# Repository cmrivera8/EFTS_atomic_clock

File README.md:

# EFTS_atomic_clock
The atomic clock described in this repository is used in the yearly European Frequency and Time Seminar (EFTS) hosted at ENSMM. This repository contains the original design files as well as the improved control software GUI in python (EFTS_atomic_clock/mac_control_program/qt_mac.py) and the microcontroller code (EFTS_atomic_clock/mac/mac.ino) embedded in the demonstrator.

When I started my contribution on this project, there were three atomic clocks, out of which only one was working correctly. The other two were marginally operational, with a weak absorption signal and low signal-to-noise ratio. This made it very difficult to lock the servo loops on the desired electronic transition. Moreover, the GUI was not intuitive and resulted in a not-ideal learning experience for the seminar attendees.

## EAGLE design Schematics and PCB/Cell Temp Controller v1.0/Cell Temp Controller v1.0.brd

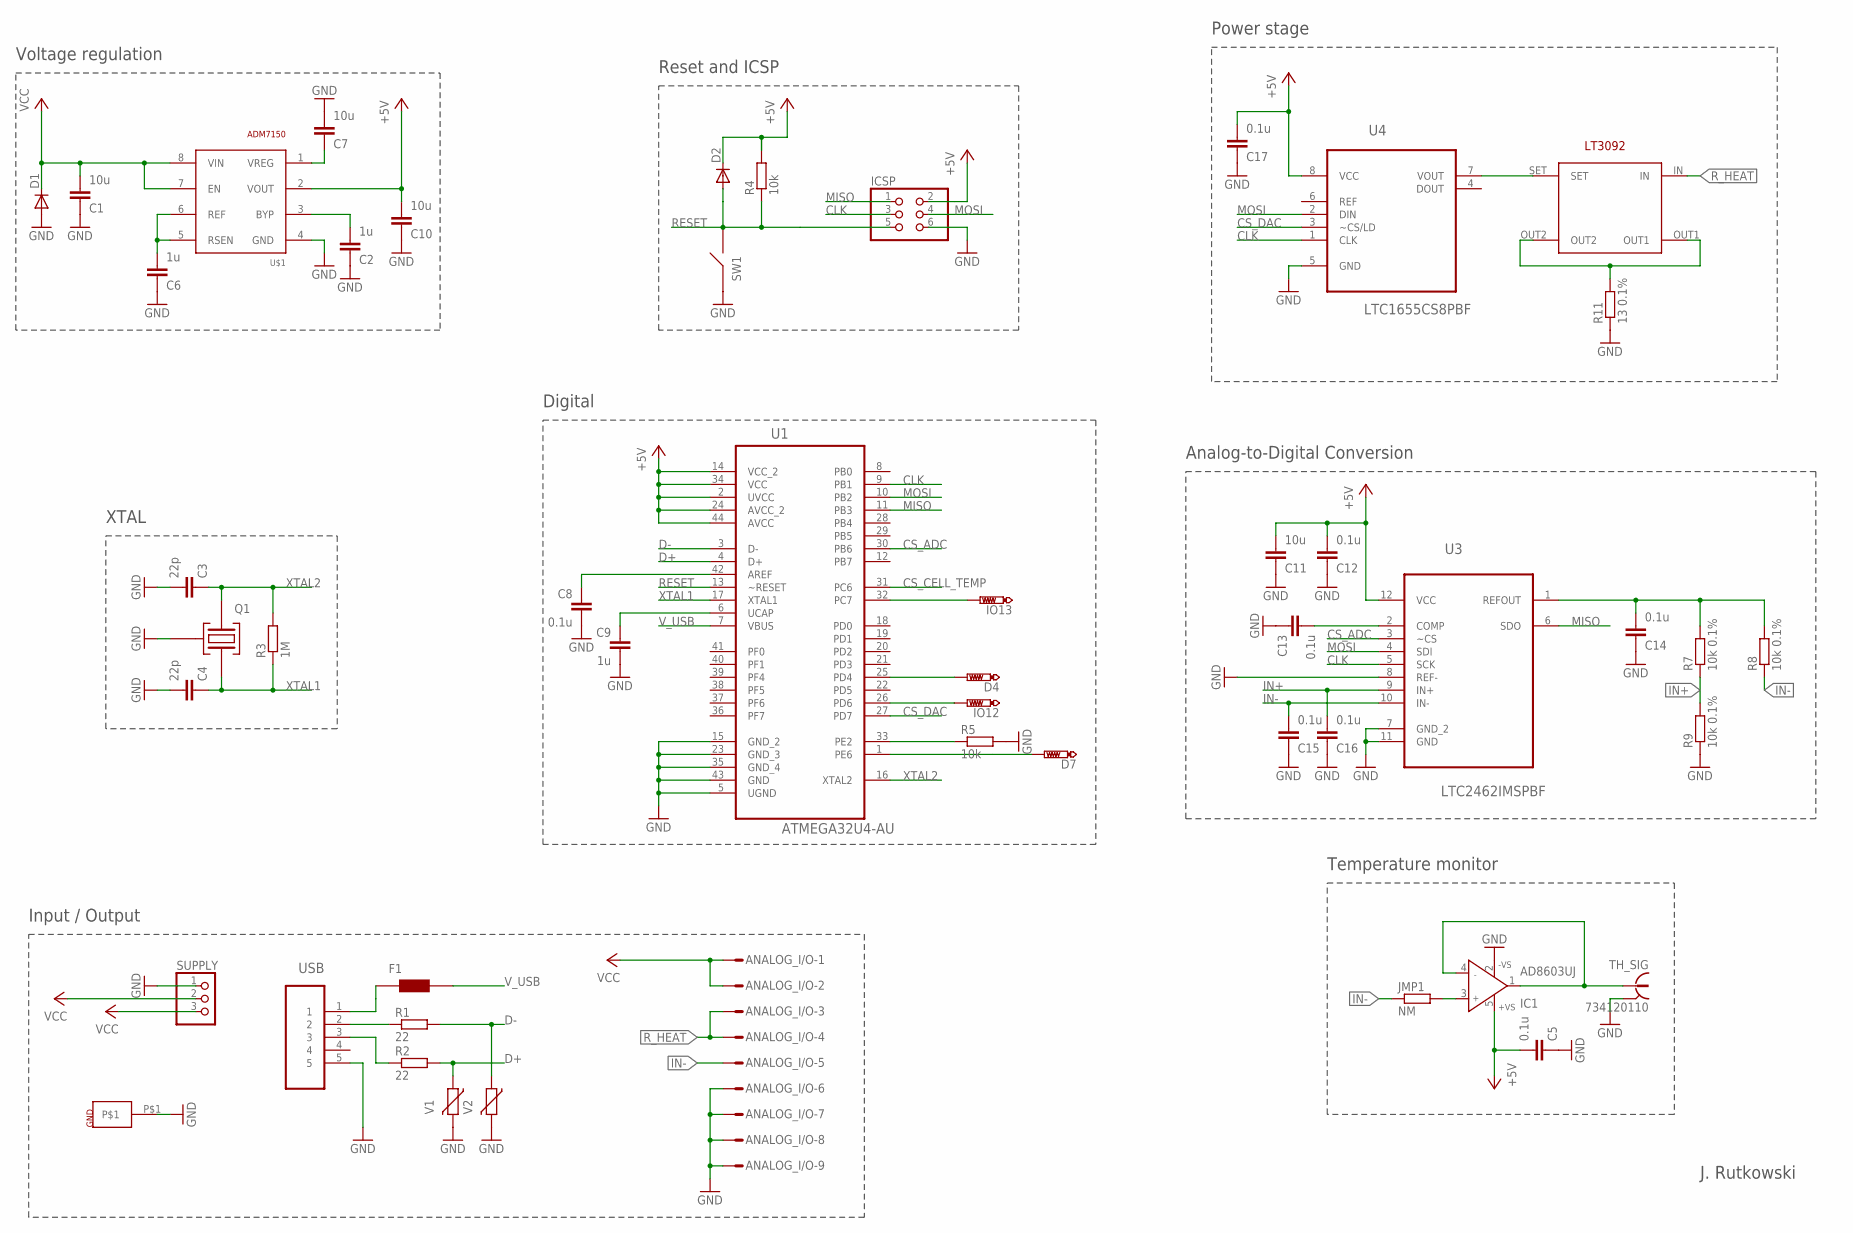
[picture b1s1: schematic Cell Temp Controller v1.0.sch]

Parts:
ANALOG_I/O: M09HPS; M09HP
C1, C7, C10, C11: 10u; C0603K
C2, C6, C9: 1u; C0603K
C3, C4: 22p; C0603K
C5, C8, C12, C13, C14, C15, C16, C17: 0.1u; C0603K
D1, D2: DIODE-SOD123; SOD123
D4, D7: PTR1PAD1-13; P1-13
F1: FUSE; C1812
IC1: AD8603UJ; SOT23-5
ICSP: PINHD-2X3; 2X03
IO12, IO13: PTR1PAD1-13; P1-13
JMP1: NM; R0402
Q1: CX2520SB; QUARTZ
R1, R2: 22; R0603
R3: 1M; R0603
R4, R5: 10k; R0603
R7, R8, R9: 10k 0.1%; R0603
R11: 13 0.1%; R2010
SUPPLY: PINHD-1X3; 1X03
SW1: B3U-1000P
TH_SIG: 734120110
U1: ATMEGA32U4-AU; QFP80P1200X1200X120-44N
U3: LTC2462IMSPBF; SOP65P490X110-12N
U4: LTC1655CS8PBF; SOIC127P600X175-8N
U$1: ADM7150; SO8
U$2: LT3092; SOT-223
U$3: GND_PAD
USB: 47346-0001; MOLEX_47346-0001
V1, V2: VARISTORCN0603; CT/CN0603

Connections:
+5V: C5.1, C10.1, C11.1, C12.1, C17.1, D2.C, IC1.5 (+VS), ICSP.2, R4.2, U1.2 (UVCC), U1.14 (VCC_2), U1.24 (AVCC_2), U1.34 (VCC), U1.44 (AVCC), U3.12 (VCC), U4.8 (VCC), U$1.2 (VOUT)
CLK: ICSP.3, U1.9 (PB1), U3.5 (SCK), U4.1 (CLK)
CS_ADC: U1.30 (PB6), U3.3 (~CS)
CS_CELL_TEMP: U1.31 (PC6)
CS_DAC: U1.27 (PD7), U4.3 (~CS/LD)
D+: R2.2, U1.4 (D+), V1.1
D-: R1.2, U1.3 (D-), V2.1
GND: ANALOG_I/O.6, ANALOG_I/O.7, ANALOG_I/O.8, ANALOG_I/O.9, C1.2, C2.2, C3.1, C4.1, C5.2, C6.2, C7.1, C8.1, C9.1, C10.2, C11.2, C12.2, C13.2, C14.2, C15.2, C16.2, C17.2, D1.A, IC1.2 (-VS), ICSP.6, Q1.2 (GND), R5.2, R9.1, R11.1, SUPPLY.1, SW1.1, TH_SIG.S@1 (2), TH_SIG.S@2 (2), TH_SIG.S@3 (2), U1.5 (UGND), U1.15 (GND_2), U1.23 (GND_3), U1.35 (GND_4), U1.43 (GND), U3.7 (GND_2), U3.8 (REF-), U3.11 (GND), U4.5 (GND), U$1.4 (GND), U$3.P$1, USB.5, V1.2, V2.2
IN+: C16.1, R7.1, R9.2, U3.9 (IN+)
IN-: ANALOG_I/O.5, C15.1, JMP1.1, R8.1, U3.10 (IN-)
MISO: ICSP.1, U1.11 (PB3), U3.6 (SDO)
MOSI: ICSP.4, U1.10 (PB2), U3.4 (SDI), U4.2 (DIN)
unnamed: F1.2 (XTAL2), USB.1
unnamed: R1.1, USB.2
unnamed: R2.1, USB.3
unnamed: U4.7 (VOUT), U$2.SET
unnamed: C8.2, U1.42 (AREF)
unnamed: C9.2, U1.6 (UCAP)
unnamed: R5.1, U1.33 (PE2)
unnamed: IO13.TP, U1.32 (PC7)
unnamed: D7.TP, U1.1 (PE6)
unnamed: C13.1, U3.2 (COMP)
unnamed: C14.1, R7.2, R8.2, U3.1 (REFOUT)
unnamed: D4.TP, U1.25 (PD4)
unnamed: IC1.1 (OUT), IC1.4 (IN-), TH_SIG.1
unnamed: IC1.3 (IN+), JMP1.2
unnamed: R11.2, U$2.OUT1, U$2.OUT2
unnamed: IO12.TP, U1.26 (PD6)
unnamed: C6.1, U$1.5 (RSEN), U$1.6 (REF)
unnamed: C7.2, U$1.1 (VREG)
unnamed: C2.1, U$1.3 (BYP)
RESET: D2.A, ICSP.5, R4.1, SW1.2, U1.13 (~RESET)
R_HEAT: ANALOG_I/O.3, ANALOG_I/O.4, U$2.IN
VCC: ANALOG_I/O.1, ANALOG_I/O.2, C1.1, D1.C, SUPPLY.2, SUPPLY.3, U$1.7 (EN), U$1.8 (VIN)
V_USB: F1.1 (XTAL1), U1.7 (VBUS)
XTAL1: C4.2, Q1.3 (XTAL2), R3.1, U1.17 (XTAL1)
XTAL2: C3.2, Q1.1 (XTAL1), R3.2, U1.16 (XTAL2)

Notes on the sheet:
Voltage regulation
XTAL
Digital
Reset and ICSP
Input / Output
Power stage
Analog-to-Digital Conversion
Temperature monitor
J. Rutkowski

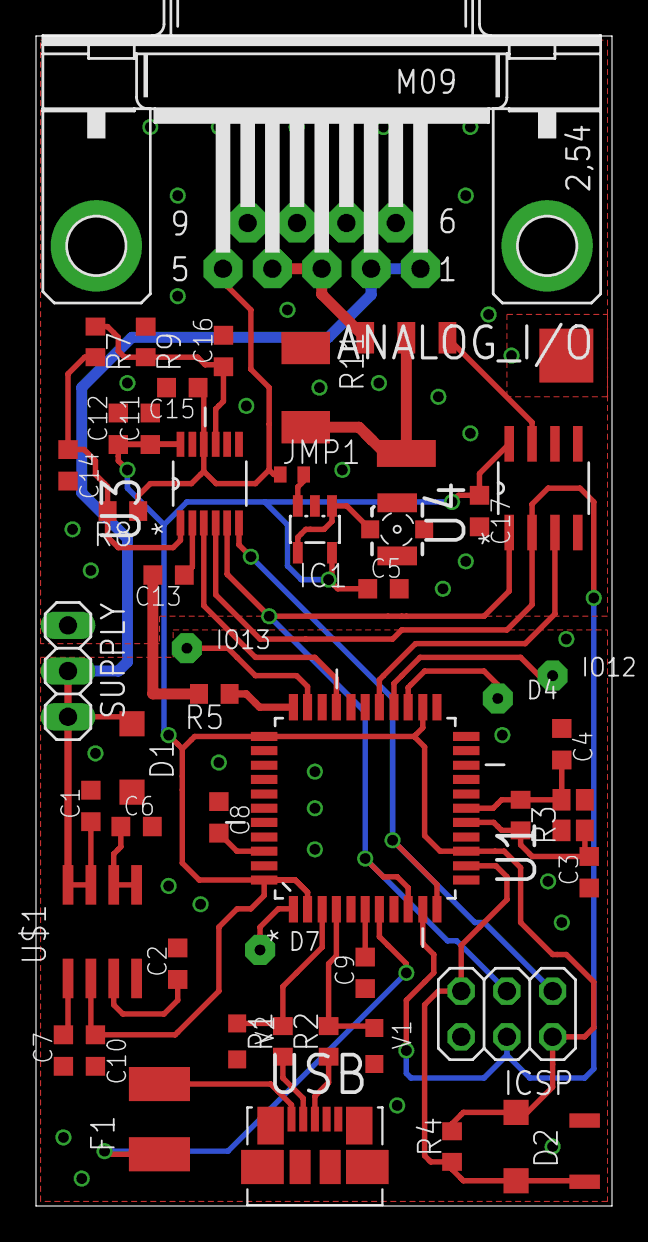
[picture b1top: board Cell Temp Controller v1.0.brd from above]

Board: 2 copper layers, 32.0 x 65.0 mm, 50 parts (0 on the bottom side), 36 nets.

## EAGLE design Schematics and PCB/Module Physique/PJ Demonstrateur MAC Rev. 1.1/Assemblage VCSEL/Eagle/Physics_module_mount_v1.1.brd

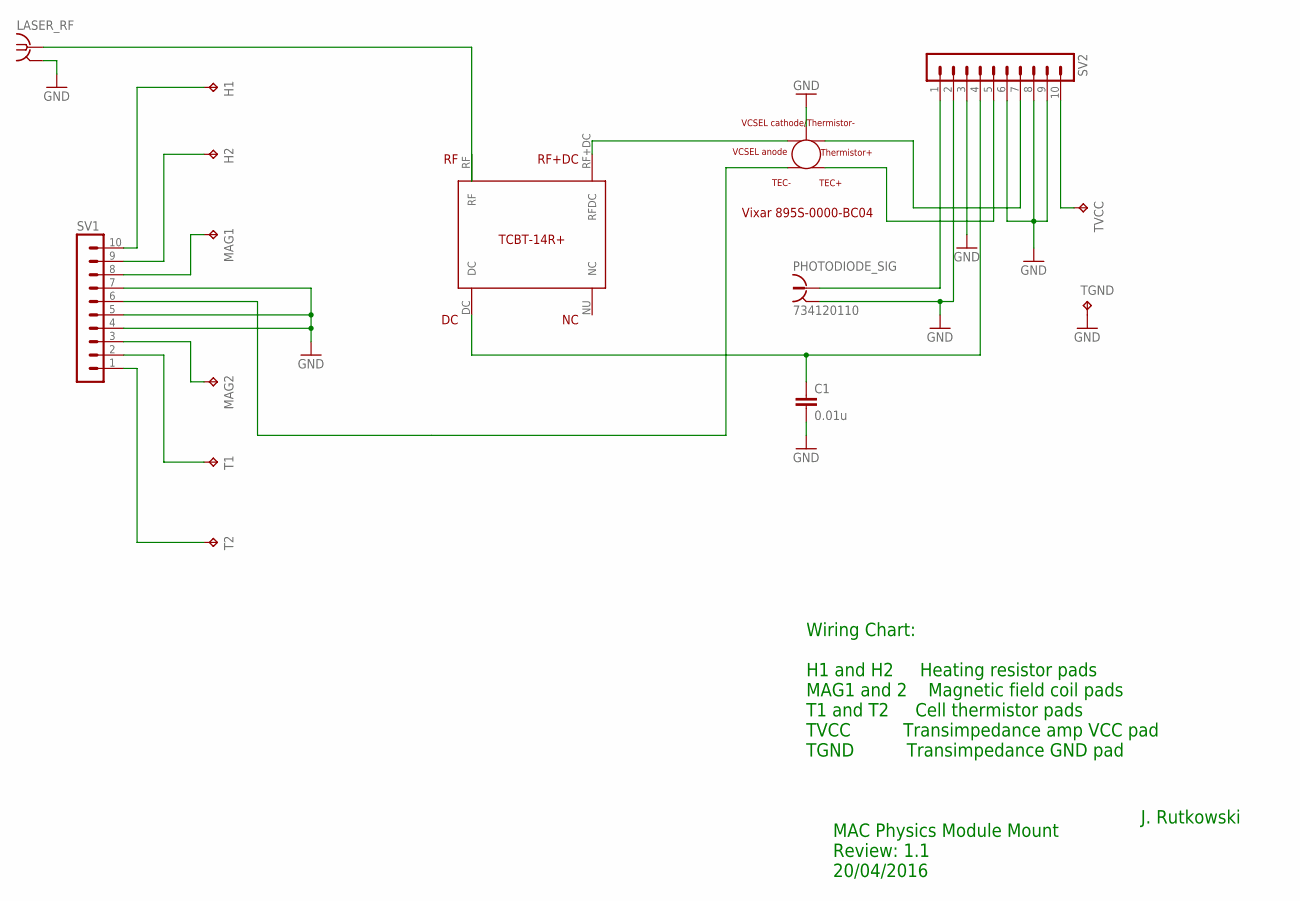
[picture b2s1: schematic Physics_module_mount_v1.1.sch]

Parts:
C1: 0.01u; C0603K
H1, H2: TPPAD1-13; P1-13
LASER_RF: SMA-142-0711-871/876; J502-ND-142-0711-871/876
MAG1, MAG2: TPPAD1-13; P1-13
PHOTODIODE_SIG: 734120110
Q1: VIXAR_895NM_VCSEL_TO46_6PIN; TO45_THT_SMD
SV1, SV2: MA10-1
T1, T2: TPPAD1-13; P1-13
TGND: TPPAD1-13; P1-13
TVCC: TPPAD1-13; P1-13
U1: TCBT-14+; TCBT_14_PAC

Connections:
GND: C1.2, LASER_RF.G@1 (2), LASER_RF.G@2 (2), LASER_RF.G@3 (2), LASER_RF.G@4 (2), PHOTODIODE_SIG.S@1 (2), PHOTODIODE_SIG.S@2 (2), PHOTODIODE_SIG.S@3 (2), Q1.LD_CATHODE_THERM (VCSEL_CATHODE/THERMISTOR-/CASE), SV1.4, SV1.5, SV1.7, SV2.2, SV2.3, SV2.6, SV2.8, SV2.9, TGND.TP
unnamed: H1.TP, SV1.10
unnamed: H2.TP, SV1.9
unnamed: MAG1.TP, SV1.8
unnamed: PHOTODIODE_SIG.1, SV2.1
unnamed: SV1.2, T1.TP
unnamed: SV1.1, T2.TP
unnamed: SV2.10, TVCC.TP
unnamed: LASER_RF.1, U1.RF
unnamed: Q1.LD_ANODE (VCSEL_ANODE), U1.RF+DC (RFDC)
unnamed: C1.1, SV2.4, U1.DC
unnamed: Q1.THERMISTOR (THERMISTOR+), SV2.7
unnamed: Q1.TEC+, SV2.5
unnamed: Q1.TEC-, SV1.6
unnamed: MAG2.TP, SV1.3

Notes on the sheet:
MAC Physics Module Mount Review: 1.1 20/04/2016
J. Rutkowski
Wiring Chart: H1 and H2 Heating resistor pads MAG1 and 2 Magnetic field coil pads T1 and T2 Cell thermistor pads TVCC Transimpedance amp VCC pad TGND Transimpedance GND pad

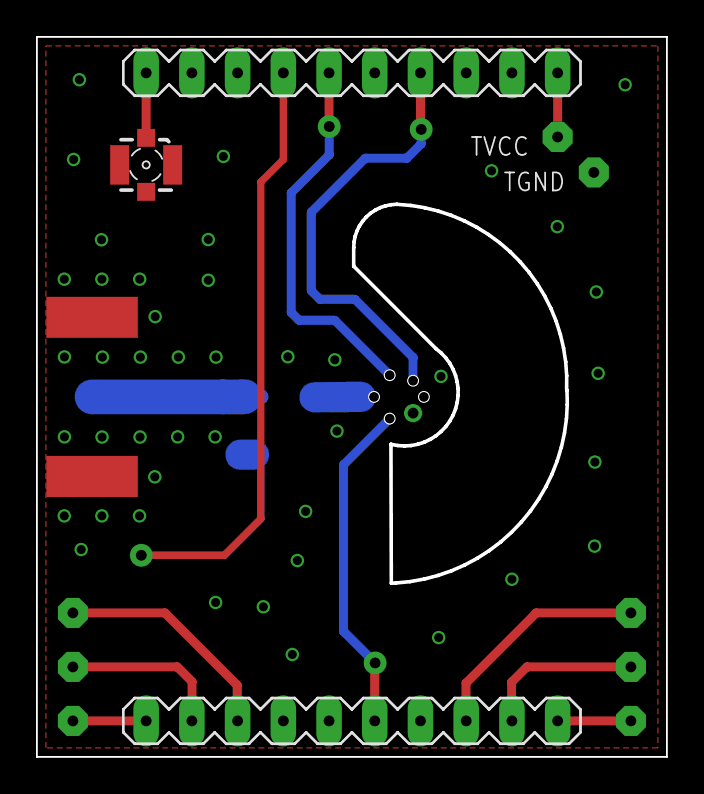
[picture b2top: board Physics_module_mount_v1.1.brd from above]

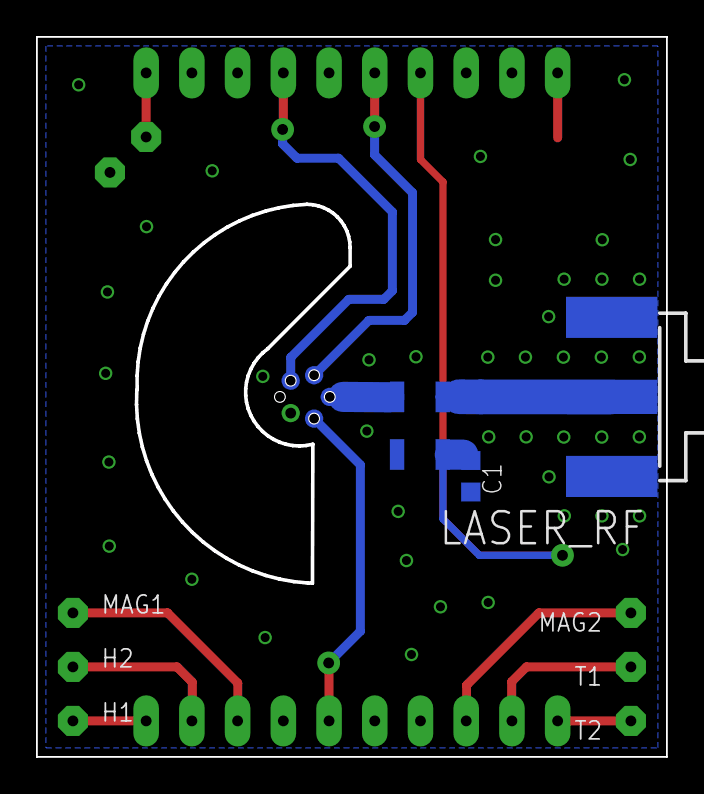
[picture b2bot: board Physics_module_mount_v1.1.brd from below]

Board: 2 copper layers, 34.9 x 39.9 mm, 15 parts (10 on the bottom side), 15 nets.

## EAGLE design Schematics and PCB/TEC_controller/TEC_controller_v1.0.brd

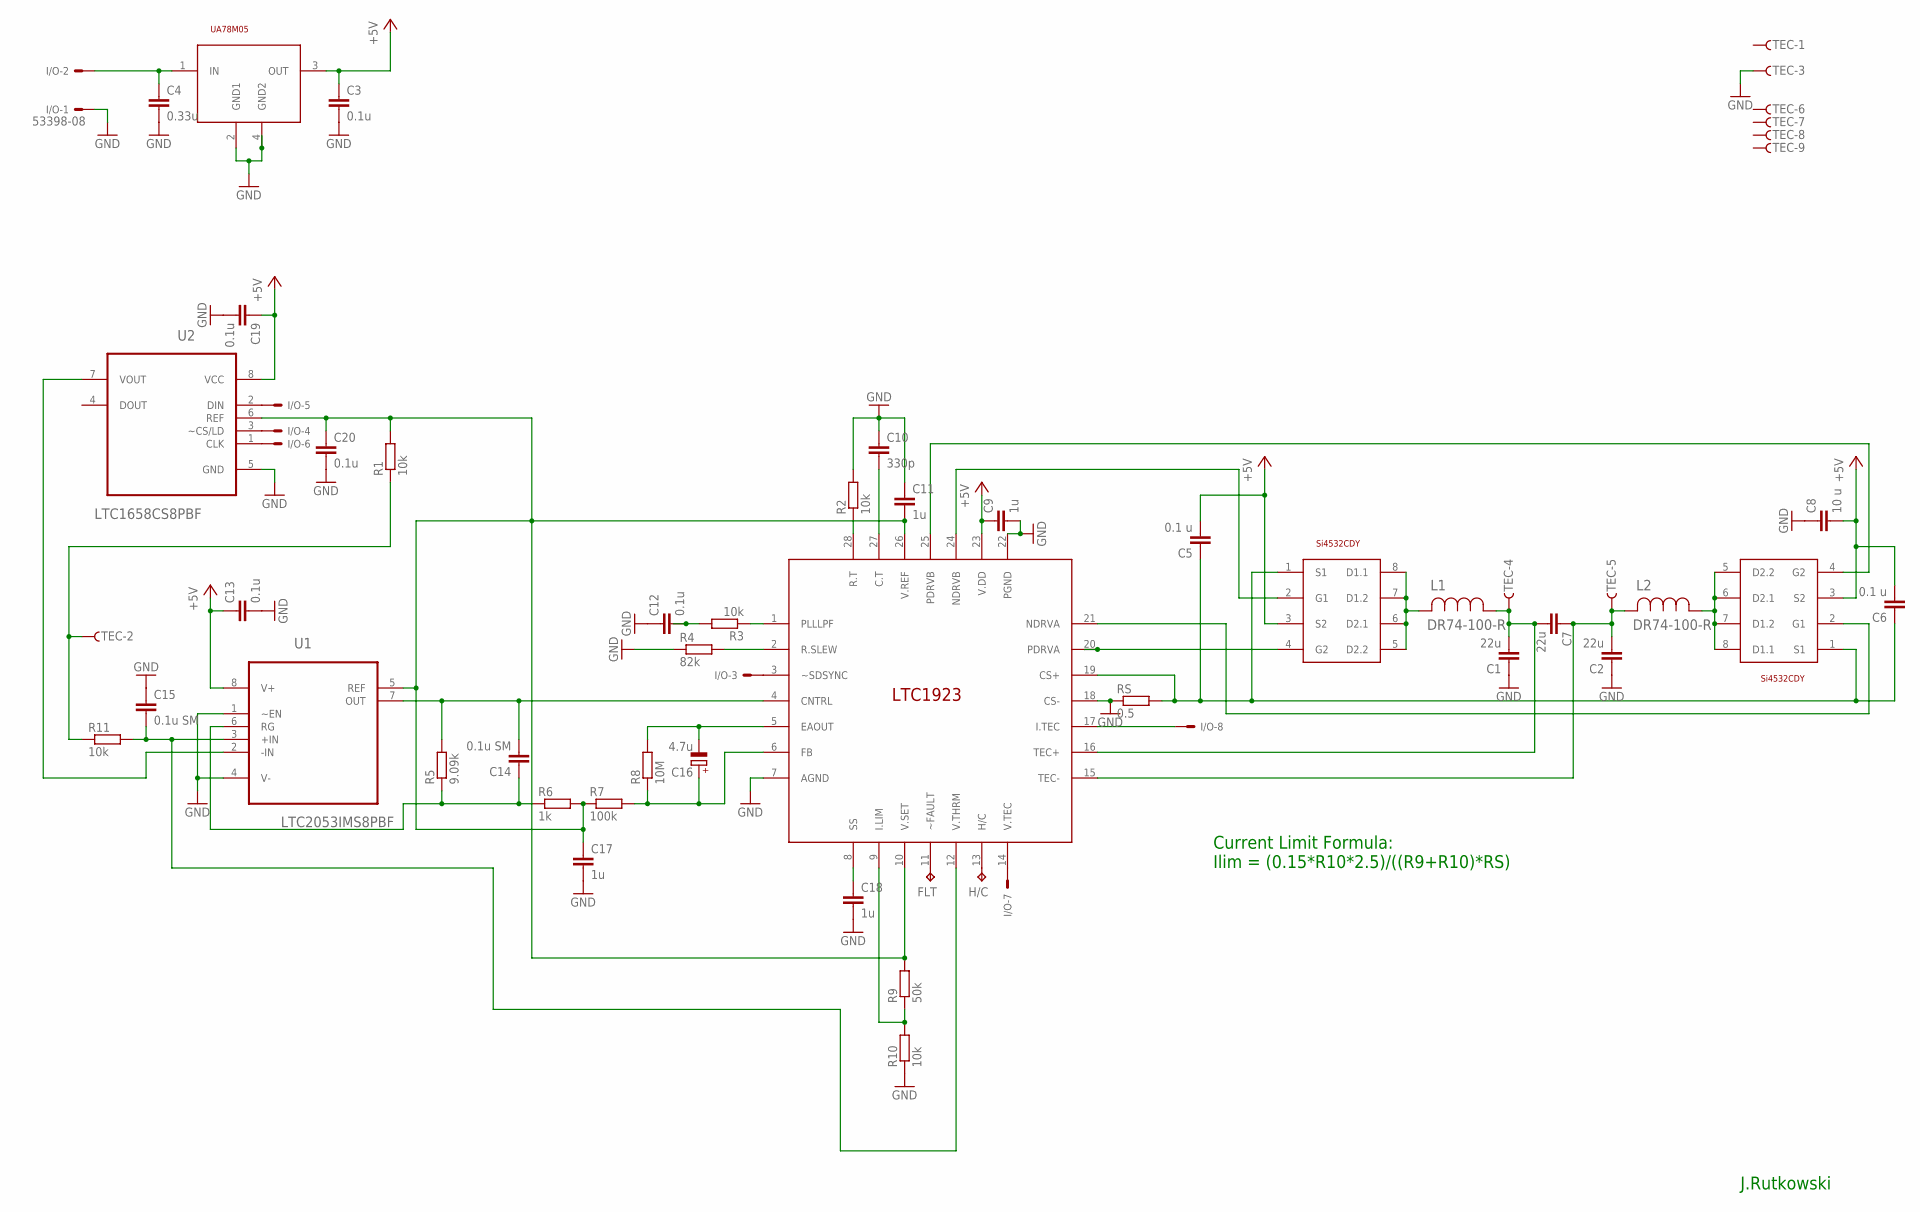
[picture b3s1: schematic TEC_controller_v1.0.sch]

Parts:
C1, C2, C7: 22u; C1210K
C3: 0.1u; C0805K
C4: 0.33u; C0805K
C5, C6: 0.1 u; C0805K
C8: 10 u; C1206K
C9, C11, C17, C18: 1u; C0603K
C10: 330p; C0603K
C12, C19, C20: 0.1u; C0603K
C13: 0.1u; C0603
C14, C15: 0.1u SM; C1210
C16: 4.7u; A/3216-18W
FLT: TPTP17SQ; TP17SQ
H/C: TPTP17SQ; TP17SQ
I/O: 53398-08
L1, L2: DR74-100-R; INDM7676X435N
R1, R2, R3, R10, R11: 10k; R0603
R4: 82k; R0603
R5: 9.09k; R0603
R6: 1k; R0603
R7: 100k; R0603
R8: 10M; R0603
R9: 50k; R0603
RS: 0.5; R1206
TEC: F09HPS; F09HP
U1: LTC2053IMS8PBF; SOP65P490X110-8N
U2: LTC1658CS8PBF; SOIC127P600X175-8N
U$1: LTC1923; SSOP28
U$2, U$3: SI4532CDY; SOIC127P600X175-8N
U$6: UA78M05; SOT-223

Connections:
+5V: C3.1, C5.2, C6.2, C8.2, C9.1, C13.1, C19.1, U1.8 (V+), U2.8 (VCC), U$1.23 (V.DD), U$2.3 (S2), U$3.3 (S2), U$6.3 (OUT)
GND: C1.1, C2.1, C3.2, C4.2, C8.1, C9.2, C10.1, C11.1, C12.1, C13.2, C15.1, C17.2, C18.2, C19.2, C20.2, I/O.1, R2.2, R4.1, R10.1, RS.1, TEC.3, U1.1 (~EN), U1.4 (V-), U2.5 (GND), U$1.7 (AGND), U$1.18 (CS-), U$1.22 (PGND), U$6.2 (GND1), U$6.4 (GND2)
unnamed: U$1.20 (PDRVA), U$2.4 (G2)
unnamed: C4.1, I/O.2, U$6.1 (IN)
unnamed: U$1.24 (NDRVB), U$2.2 (G1)
unnamed: L1.2, U$2.5 (D2.2), U$2.6 (D2.1), U$2.7 (D1.2), U$2.8 (D1.1)
unnamed: C1.2, C7.2, L1.1, TEC.4, U$1.16 (TEC+)
unnamed: L2.1, U$3.5 (D2.2), U$3.6 (D2.1), U$3.7 (D1.2), U$3.8 (D1.1)
unnamed: C5.1, C6.1, RS.2, U$1.19 (CS+), U$2.1 (S1), U$3.1 (S1)
unnamed: U$1.21 (NDRVA), U$3.2 (G1)
unnamed: C2.2, C7.1, L2.2, TEC.5, U$1.15 (TEC-)
unnamed: U$1.25 (PDRVB), U$3.4 (G2)
unnamed: I/O.4, U2.3 (~CS/LD)
unnamed: R2.1, U$1.28 (R.T)
unnamed: I/O.8, U$1.17 (I.TEC)
unnamed: C10.2, U$1.27 (C.T)
unnamed: I/O.7, U$1.14 (V.TEC)
unnamed: I/O.3, U$1.3 (~SDSYNC)
unnamed: I/O.5, U2.2 (DIN)
unnamed: I/O.6, U2.1 (CLK)
unnamed: H/C.TP, U$1.13 (H/C)
unnamed: R3.1, U$1.1 (PLLLPF)
unnamed: C12.2, R3.2
unnamed: R4.2, U$1.2 (R.SLEW)
unnamed: C14.2, R5.2, U1.7 (OUT), U$1.4 (CNTRL)
unnamed: C14.1, R5.1, R6.1, U1.6 (RG)
unnamed: FLT.TP, U$1.11 (~FAULT)
unnamed: C18.1, U$1.8 (SS)
unnamed: C15.2, R11.2, U1.3 (+IN), U$1.12 (V.THRM)
unnamed: C16.+, R7.2, R8.1, U$1.6 (FB)
unnamed: C16.-, R8.2, U$1.5 (EAOUT)
unnamed: R9.1, R10.2, U$1.9 (I.LIM)
unnamed: R1.1, R11.1, TEC.2
unnamed: U1.2 (-IN), U2.7 (VOUT)
unnamed: C11.2, C17.1, C20.1, R1.2, R6.2, R7.1, R9.2, U1.5 (REF), U2.6 (REF), U$1.10 (V.SET), U$1.26 (V.REF)

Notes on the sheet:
J.Rutkowski
Current Limit Formula: Ilim = (0.15*R10*2.5)/((R9+R10)*RS)

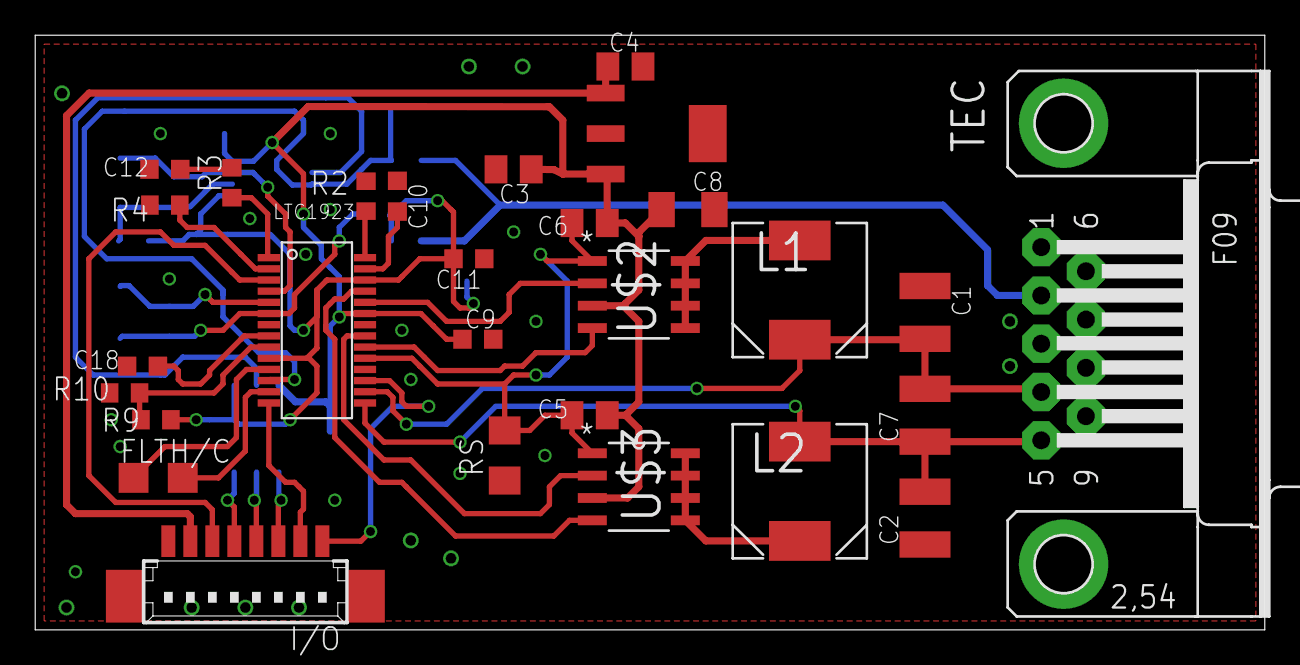
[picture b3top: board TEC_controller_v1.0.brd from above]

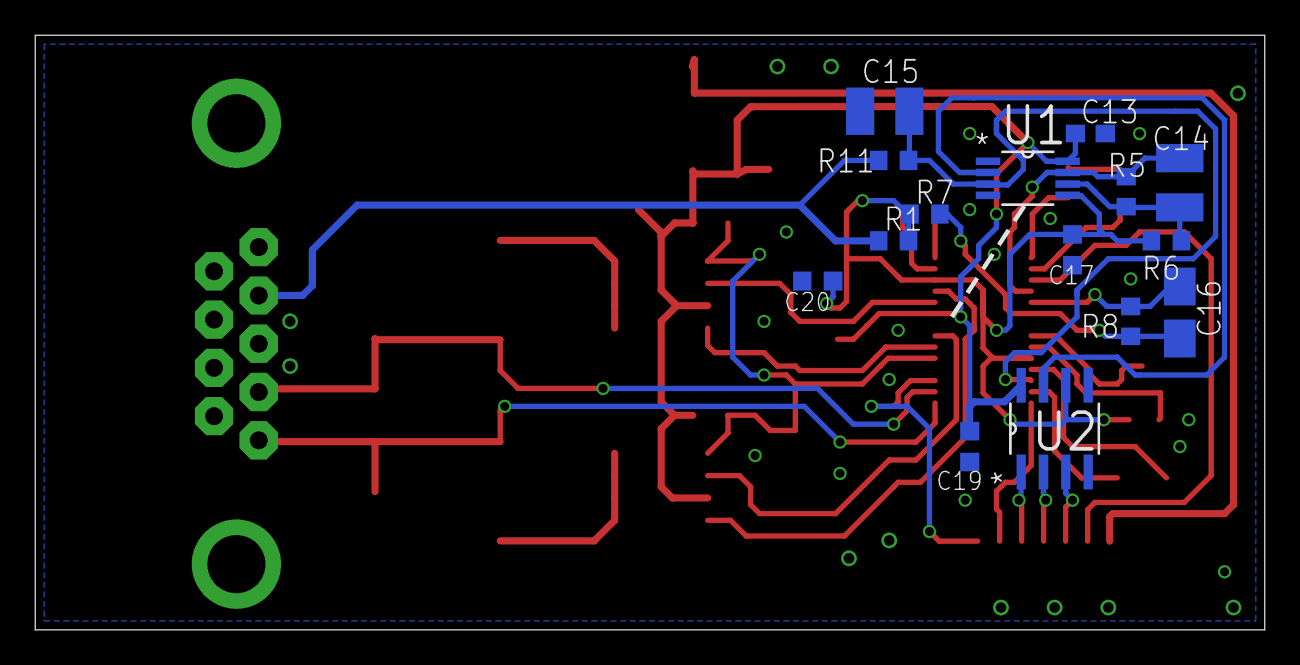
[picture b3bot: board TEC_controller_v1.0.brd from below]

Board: 2 copper layers, 69.8 x 33.8 mm, 44 parts (15 on the bottom side), 35 nets.

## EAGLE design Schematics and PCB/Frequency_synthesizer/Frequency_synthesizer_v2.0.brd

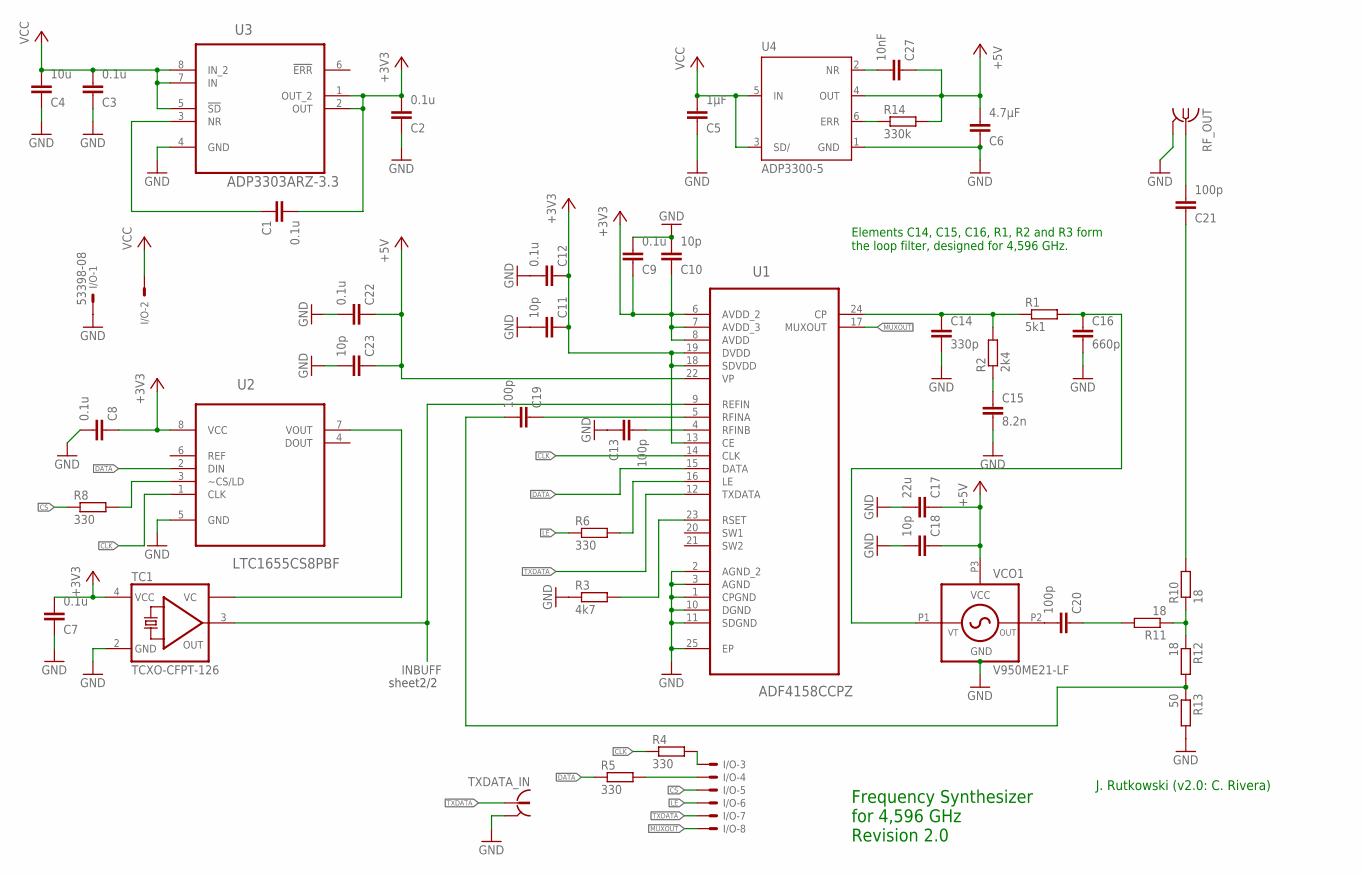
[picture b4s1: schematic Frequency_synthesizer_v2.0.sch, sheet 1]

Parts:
C1, C2, C3, C7, C8, C9, C12, C22: 0.1u; C0603K
C4: 10u; C0805K
C5: 1µF; C0603K
C6: 4.7µF; C0603K
C10, C11, C18, C23: 10p; C0603K
C13, C19, C20, C21: 100p; C0402
C14: 330p; C0603K
C15: 8.2n; C0603K
C16: 660p; C0603K
C17: 22u; C0805
C27: 10nF; C0603K
I/O: 53398-08
R1: 5k1; R0603
R2: 2k4; R0603
R3: 4k7; R0603
R4, R5, R6, R8: 330; R0603
R10, R11, R12: 18; R0402
R13: 50; R0402
R14: 330k; R0603
RF_OUT: SMA-142-0711-871/876; J502-ND-142-0711-871/876
TC1: TCXO-CFPT-126; 7.0X5.0-4-PAD
TXDATA_IN: 734120110
U1: ADF4158CCPZ; QFN50P400X400X80-25N
U2: LTC1655CS8PBF; SOIC127P600X175-8N
U3: ADP3303ARZ-3.3; SOIC127P600X175-8N
U4: ADP3300-5; SOT23-6
VCO1: V950ME21-LF; MINI-14S

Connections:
+3V3: C1.1, C2.1, C7.1, C8.2, C9.2, C10.2, C11.2, C12.2, TC1.4 (VCC), U1.6 (AVDD_2), U1.7 (AVDD_3), U1.8 (AVDD), U1.13 (CE), U1.18 (SDVDD), U1.19 (DVDD), U2.8 (VCC), U3.1 (OUT_2), U3.2 (OUT); also elsewhere on the board
+5V: C6.1, C17.2, C18.2, C22.2, C23.2, C27.2, R14.2, U1.22 (VP), U4.4 (OUT), VCO1.P3 (VCC)
CLK: R4.1, U1.14 (CLK), U2.1 (CLK)
CS: I/O.5, R8.1
DATA: R5.1, U1.15 (DATA), U2.2 (DIN)
GND: C2.2, C3.2, C4.2, C5.2, C6.2, C7.2, C8.1, C9.1, C10.1, C11.1, C12.1, C13.2, C14.2, C15.2, C16.2, C17.1, C18.1, C22.1, C23.1, I/O.1, R3.1, R13.2, RF_OUT.G@1 (2), RF_OUT.G@2 (2), RF_OUT.G@3 (2), RF_OUT.G@4 (2), TC1.2 (GND), TXDATA_IN.S@1 (2), TXDATA_IN.S@2 (2), TXDATA_IN.S@3 (2), U1.1 (CPGND), U1.2 (AGND_2), U1.3 (AGND), U1.10 (DGND), U1.11 (SDGND), U1.25 (EP), U2.5 (GND), U3.4 (GND), U4.1 (GND), VCO1.S1, VCO1.S2, VCO1.S3, VCO1.S4, VCO1.S5, VCO1.S6, VCO1.S7, VCO1.S8, VCO1.S9, VCO1.S10, VCO1.S11; also elsewhere on the board
INBUFF: TC1.3 (OUT), U1.9 (REFIN); also elsewhere on the board
LE: I/O.6, R6.1
MUXOUT: I/O.8, U1.17 (MUXOUT)
unnamed: C14.1, R1.1, R2.2, U1.24 (CP)
unnamed: C16.1, R1.2, VCO1.P1 (VT)
unnamed: C1.2, U3.3 (NR)
unnamed: C15.1, R2.1
unnamed: C13.1, U1.4 (RFINB)
unnamed: R8.2, U2.3 (~CS/LD)
unnamed: I/O.4, R5.2
unnamed: I/O.3, R4.2
unnamed: R14.1, U4.6 (ERR)
unnamed: TC1.1 (VC), U2.7 (VOUT)
unnamed: R6.2, U1.16 (LE)
unnamed: R3.2, U1.23 (RSET)
unnamed: C20.1, VCO1.P2 (OUT)
unnamed: C20.2, R11.2
unnamed: R10.1, R11.1, R12.1
unnamed: C19.1, R12.2, R13.1
unnamed: C21.2, R10.2
unnamed: C21.1, RF_OUT.1
unnamed: C19.2, U1.5 (RFINA)
unnamed: C27.1, U4.2 (NR)
TXDATA: I/O.7, TXDATA_IN.1, U1.12 (TXDATA)
VCC: C3.1, C4.1, C5.1, I/O.2, U3.5 (!SD), U3.7 (IN), U3.8 (IN_2), U4.3 (SD/), U4.5 (IN)

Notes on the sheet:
J. Rutkowski (v2.0: C. Rivera)
Elements C14, C15, C16, R1, R2 and R3 form the loop filter, designed for 4,596 GHz.
Frequency Synthesizer for 4,596 GHz Revision 2.0
sheet2/2

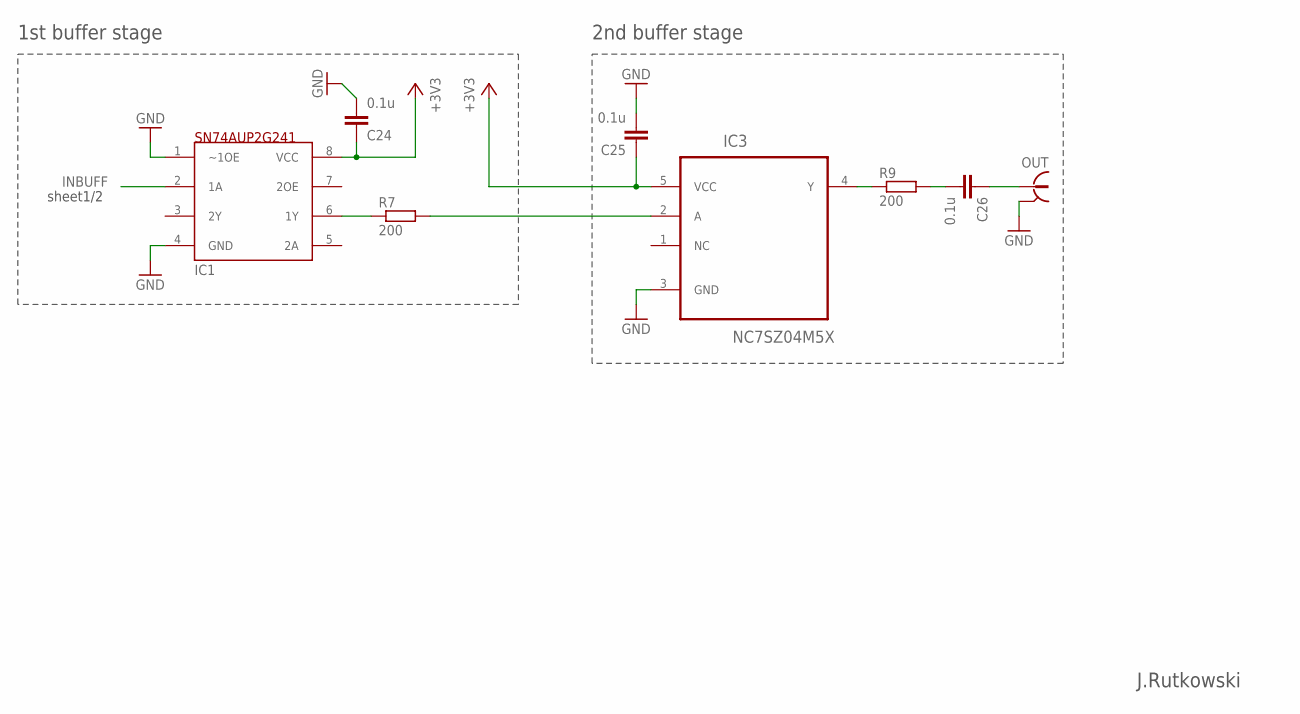
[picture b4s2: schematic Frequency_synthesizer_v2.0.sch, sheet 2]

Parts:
C24, C25, C26: 0.1u; C0603K
IC1: SN74AUP2G241; DCU_(R-PDSO-G8)
IC3: NC7SZ04M5X; SOT95P280X145-5N
OUT: 734120110
R7, R9: 200; R0603

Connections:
+3V3: C24.2, C25.2, IC1.8 (VCC), IC3.5 (VCC); also elsewhere on the board
GND: C24.1, C25.1, IC1.1 (~1OE), IC1.4 (GND), IC3.3 (GND), OUT.S@1 (2), OUT.S@2 (2), OUT.S@3 (2); also elsewhere on the board
INBUFF: IC1.2 (1A); also elsewhere on the board
unnamed: IC1.6 (1Y), R7.1
unnamed: IC3.2 (A), R7.2
unnamed: IC3.4 (Y), R9.1
unnamed: C26.1, R9.2
unnamed: C26.2, OUT.1

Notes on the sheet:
1st buffer stage
J.Rutkowski
2nd buffer stage
sheet1/2

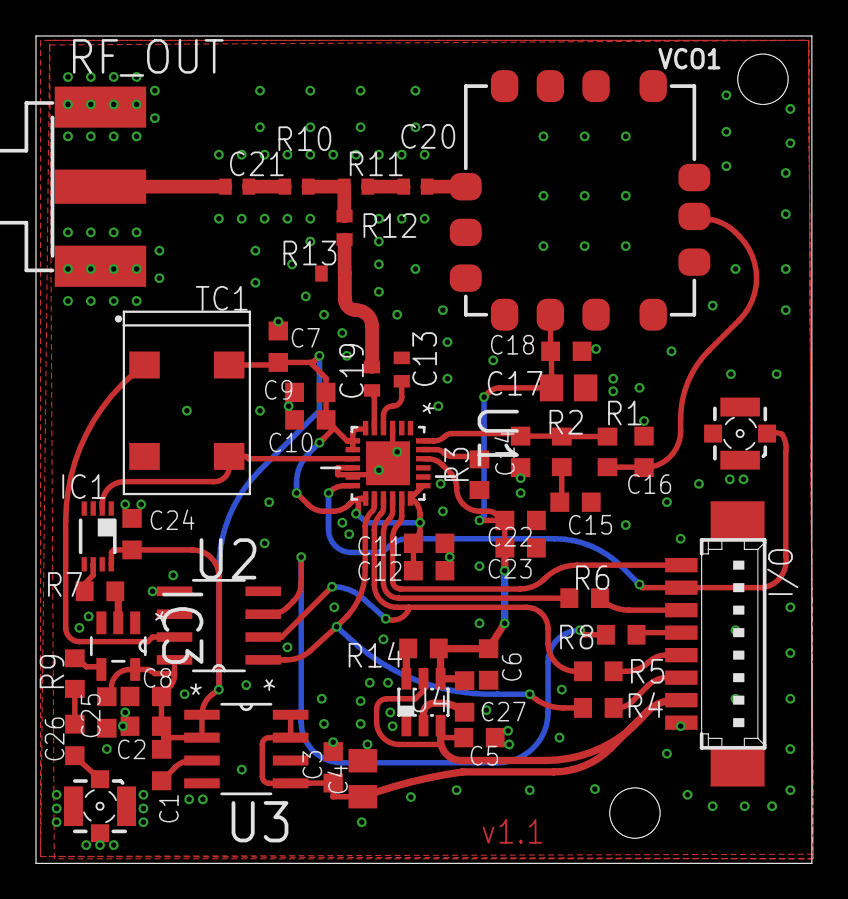
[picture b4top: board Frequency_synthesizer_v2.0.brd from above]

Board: 2 copper layers, 43.1 x 46.0 mm, 53 parts (0 on the bottom side), 36 nets.

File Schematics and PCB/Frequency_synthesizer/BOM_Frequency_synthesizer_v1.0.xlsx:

Bill of Materials
Assembly Name: | Frequency synthesizer
Revision: | 1.0
Date: | 42493
Part Name | Value | Package | Description | Manufacturer | MPN | Ref. Farnell | Quantity | Approx. Unit Price
C1, C2, C3, C6, C7, C8, C9, C12, C22 | 0.1u | 0603 | Condensateur céramique multicouche CMS, 0.1 µF, ± 10%, X7R, 50 V, 0603 [1608 Me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 | WALSIN | 0603B104K500CT | 2496834 | 9 | 0.0126
C4 | 10u | 0805 | Condensateur céramique multicouche CMS, Série GRM, 10 µF, ± 10%, X5R, 25 V, 080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 | MURATA | GRM219R61E106KA12D | 2426961 | 1 | 0.129
C5 | 0.33u | 0603 | Condensateur céramique multicouche CMS, Série C, 0.33 µF, ± 10%, X5R, 25 V, 060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 | TDK | C1608X5R1E334K080AC | 2346893 | 1 | 0.0822
C10, C11, C18, C23 | 10p | 0603 | Condensateur céramique multicouche CMS, Série MC, 10 pF, ± 0.5pF, C0G / NP0, 50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 | MULTICOMP | MC0603N100D500CT | 1759053 | 3 | 0.0248
C13, C19, C20, C21 | 100p | 0402 | CONDENSATEUR RF NP0 100PF 50V 0402 | MULTICOMP | MCHH15N101J500CT | 2310297 | 4 | 0.0046
C14 | 47n | 0602 | Condensateur céramique multicouche CMS, 0.047 µF, ± 5%, X7R, 25 V, 0603 [1608 M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 | WALSIN | 0603B473J250CT | 2496864 | 1 | 0.0177
C15 | 0.68u | 0603 | Condensateur céramique multicouche CMS, Série MC, 0.68 µF, ± 10%, X5R, 16 V, 06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 | MULTICOMP | MC0603X684K160CT | 1759406 | 1 | 0.0706
C16 | 22n | 0603 | Condensateur céramique multicouche CMS, 0.022 µF, ± 5%, X7R, 50 V, 0603 [1608 M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 | AVX | 06035C223JAT2A | 2332645 | 1 | 0.376
C17 | 22u | 0805 | Condensateur céramique multicouche CMS, Série GRM, 22 µF, ± 20%, X5R, 25 V, 080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 | MURATA | GRM21BR61E226ME44L | 1907510 | 1 | 0.504
R1 | 147 | 0603 | Résistance CMS, Couche mince, Série WIN, 147 ohm, 100 mW, ± 0.1%, 75 V, 0603 [1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 | WELWYN | WINT0603LF031470B | 2428794 | 1 | 0.774
R2 | 71.5 | 0603 | Résistance CMS, Couche mince, Série CPF, 71.5 ohm, 63 mW, ± 0.1%, 50 V, 0603 [1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 | TE CONNECTIVITY | CPF0603B71R5E1 | 2331358 | 1 | 0.686
R3 | 5k1 | 0603 | Résistance CMS, Couche mince, Série PCF, 5.1 kohm, 63 mW, ± 0.1%, 50 V, 0603 [1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 | WELWYN | PCF0603P-R-5K1-BT1 | 1506015 | 1 | 0.44
R4, R5, R6, R8 | 330 | 0603 | Résistance CMS, Couche épaisse, Série MCWR, 330 ohm, 100 mW, ± 1%, 50 V, 0603 [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 | MULTICOMP | MCWR06X3300FTL | 2447339 | 4 | 0.0067
R10, R11, R12 | 18 | 0402 | Résistance CMS, Couche mince, Série CPF, 18 ohm, 63 mW, ± 0.1%, 25 V, 0402 [100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 | TE CONNECTIVITY / NEOHM | CPF0402B18RE1 | 1697295 | 3 | 0.711
R13 | 50 | 0402 | RESISTANCE MICROWAVE 50R 0402 | VISHAY | FC0402E50R0BSWS | 1109049 | 1 | 3.28
I/O | - | 53398-08 | Connecteur fil-à-carte, Série PicoBlade 53398, Montage CMS, Embase, 8, 1.25 mm | MOLEX | 53398-0871 | 1125371 | 1 | 1.43
10MHZ_OUT, TXDATA_IN | - | U.FL | Connecteur coaxial / RF, Coaxial RF, Jack droit, Montage en surface vertical, 5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 | MOLEX | 73412-0110 | 1340200 | 2 | 0.784
RF_OUT | - | SMA | Connecteur coaxial / RF, Coaxial SMA, Jack droit, A souder, 50 ohm, Cuivre-béry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 | JOHNSON | 142-0701-851 | 1019325 | 1 | 4.97
TCXO | - | TCXO-CFPT-126 | OSCILLATEUR A QUARTZ CMS 10MHZ | IQD FREQUENCY PRODUCTS | LFTVXO009912 | 1100747 | 1 | 26.83
U$1 | - | SOT-223 | Linear Voltage Regulator, Fixed, 7V To 25V In, 5V And 0.5A Out | TEXAS INSTRUMENTS | UA78M05QDCYRG4Q1 | 2383041 | 1 | 0.718
U1 | - | LFCSP-24 | SYNTHETISEUR FREQUENCE 6.1GHZ LFCSP-24 | ANALOG DEVICES | ADF4158CCPZ | 2377117 | 1 | 9.94
U2 | - | SOIC-8 | Convertisseur numérique vers analogique, 16 bit, Série, 2.7V à 5.5V, SOIC, 8 | LINEAR TECHNOLOGY | LTC1655LIS8#PBF | 2294807 | 1 | 19.1
U3 | - | SOIC-8 | Régulateur LDO Tension fixe, 3.2V à 12V, 180mV Dropout, 3.3Vout, 200mAout, SOIC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 | ANALOG DEVICES | ADP3303ARZ-3.3 | 2305721 | 1 | 2.53
VCO | - | MINI-14S | Voltage-Controlled Oscillator Surface Mount Module | Z-Communications | V950ME21-LF | - | 1 | -

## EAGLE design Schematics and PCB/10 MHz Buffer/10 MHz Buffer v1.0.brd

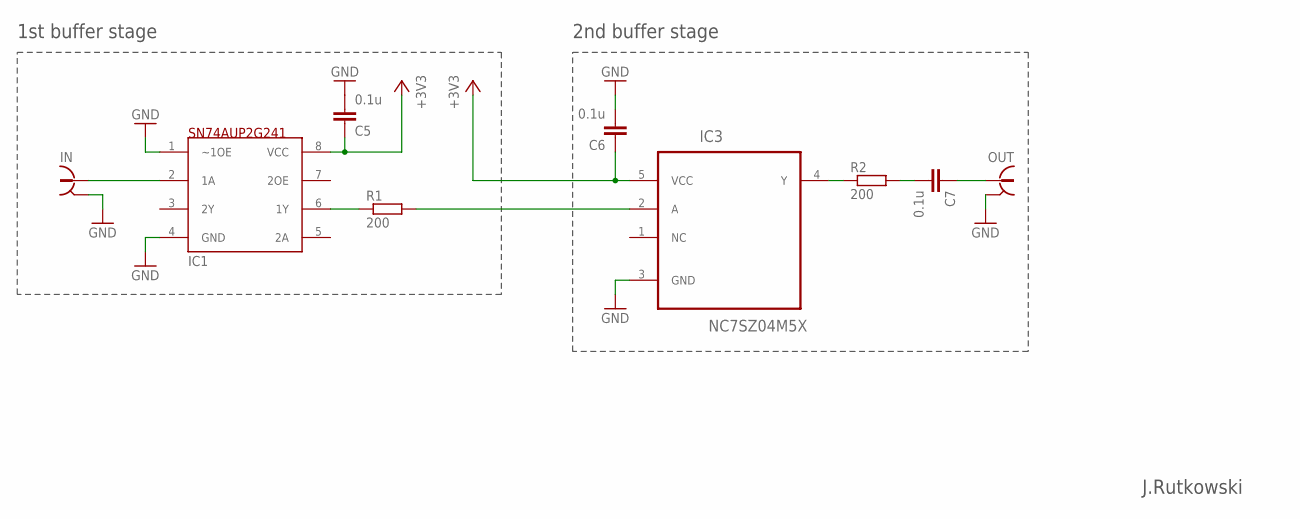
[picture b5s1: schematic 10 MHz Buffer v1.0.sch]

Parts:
C5, C6, C7: 0.1u; C0603K
IC1: SN74AUP2G241; DCU_(R-PDSO-G8)
IC3: NC7SZ04M5X; SOT95P280X145-5N
IN: 734120110
OUT: 734120110
R1, R2: 200; R0603

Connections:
+3V3: C5.2, C6.2, IC1.8 (VCC), IC3.5 (VCC)
GND: C5.1, C6.1, IC1.1 (~1OE), IC1.4 (GND), IC3.3 (GND), IN.S@1 (2), IN.S@2 (2), IN.S@3 (2), OUT.S@1 (2), OUT.S@2 (2), OUT.S@3 (2)
unnamed: IC1.2 (1A), IN.1
unnamed: IC1.6 (1Y), R1.1
unnamed: IC3.2 (A), R1.2
unnamed: IC3.4 (Y), R2.1
unnamed: C7.1, R2.2
unnamed: C7.2, OUT.1

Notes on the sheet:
1st buffer stage
J.Rutkowski
2nd buffer stage

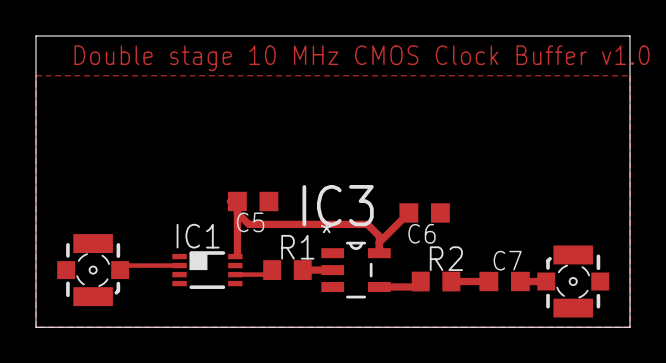
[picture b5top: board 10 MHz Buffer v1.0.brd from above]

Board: 2 copper layers, 33.0 x 16.2 mm, 9 parts (0 on the bottom side), 8 nets.

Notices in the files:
parts and their libraries:
z-comm: Copyright (C) 2008, Bob Starr
